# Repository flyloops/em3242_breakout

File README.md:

# angle_sensor_em3242 
Breakout board for the EM3242 angle sensor IC. 

* [Schematic (PDF)](angle_sensor_em3242.pdf)
* [Bill-of-materials](BOM.txt)

# Top View: 

# Bottom View:

# License: 
Creative Commons Attribution 4.0 International CC BY 4.0

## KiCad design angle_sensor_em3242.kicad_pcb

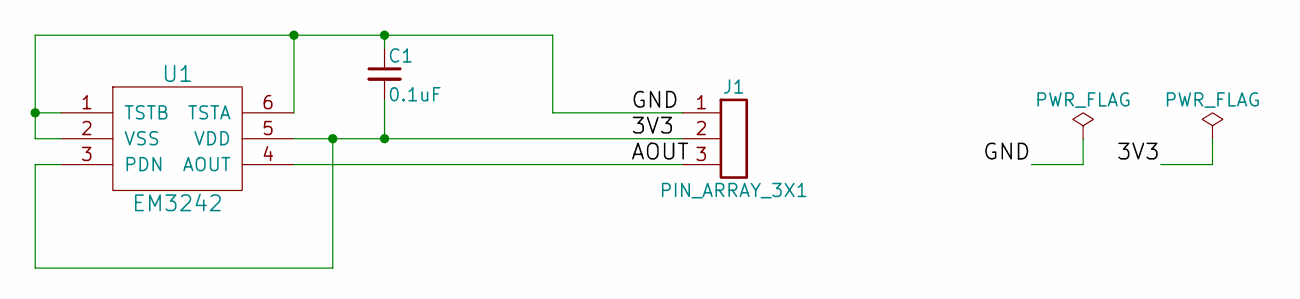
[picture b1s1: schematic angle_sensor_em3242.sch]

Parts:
C1: 0.1uF; C_0805_HandSoldering
J1: PIN_ARRAY_3X1; HEADER_3X1
U1: EM3242

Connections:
/3V3: C1.2, J1.2, U1.3 (PDN), U1.5 (VDD)
/AOUT: J1.3, U1.4 (AOUT)
/GND: C1.1, J1.1, U1.1 (TSTB), U1.2 (VSS), U1.6 (TSTA)

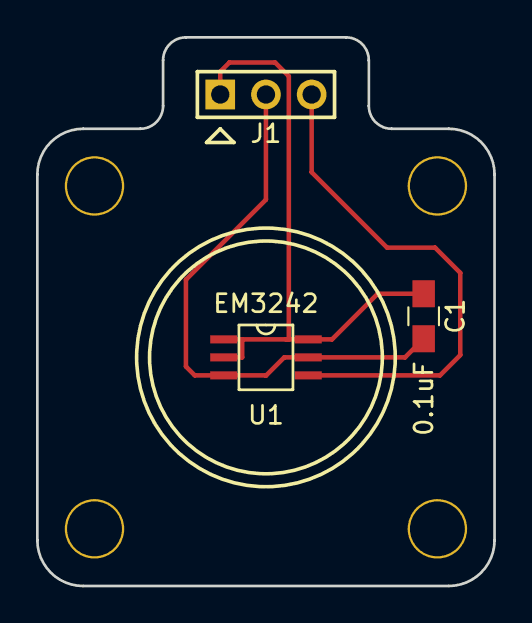
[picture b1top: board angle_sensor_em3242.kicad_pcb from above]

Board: 2 copper layers, 25.4 x 30.5 mm, 7 parts (0 on the bottom side), 3 nets.

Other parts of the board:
M1, M2, M3, M4: VAL**; MOUNT_HOLE_4_40

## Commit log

2018-01-13 Project creation.
2018-01-17 Added marking for pin #1 on sensor headers.
2018-01-17 Added PDF of schematic and link in README.
2018-01-17 Added bill-of-materials and link to it in README.
2018-01-17 Changed Digikey part number to one with no require minium.
